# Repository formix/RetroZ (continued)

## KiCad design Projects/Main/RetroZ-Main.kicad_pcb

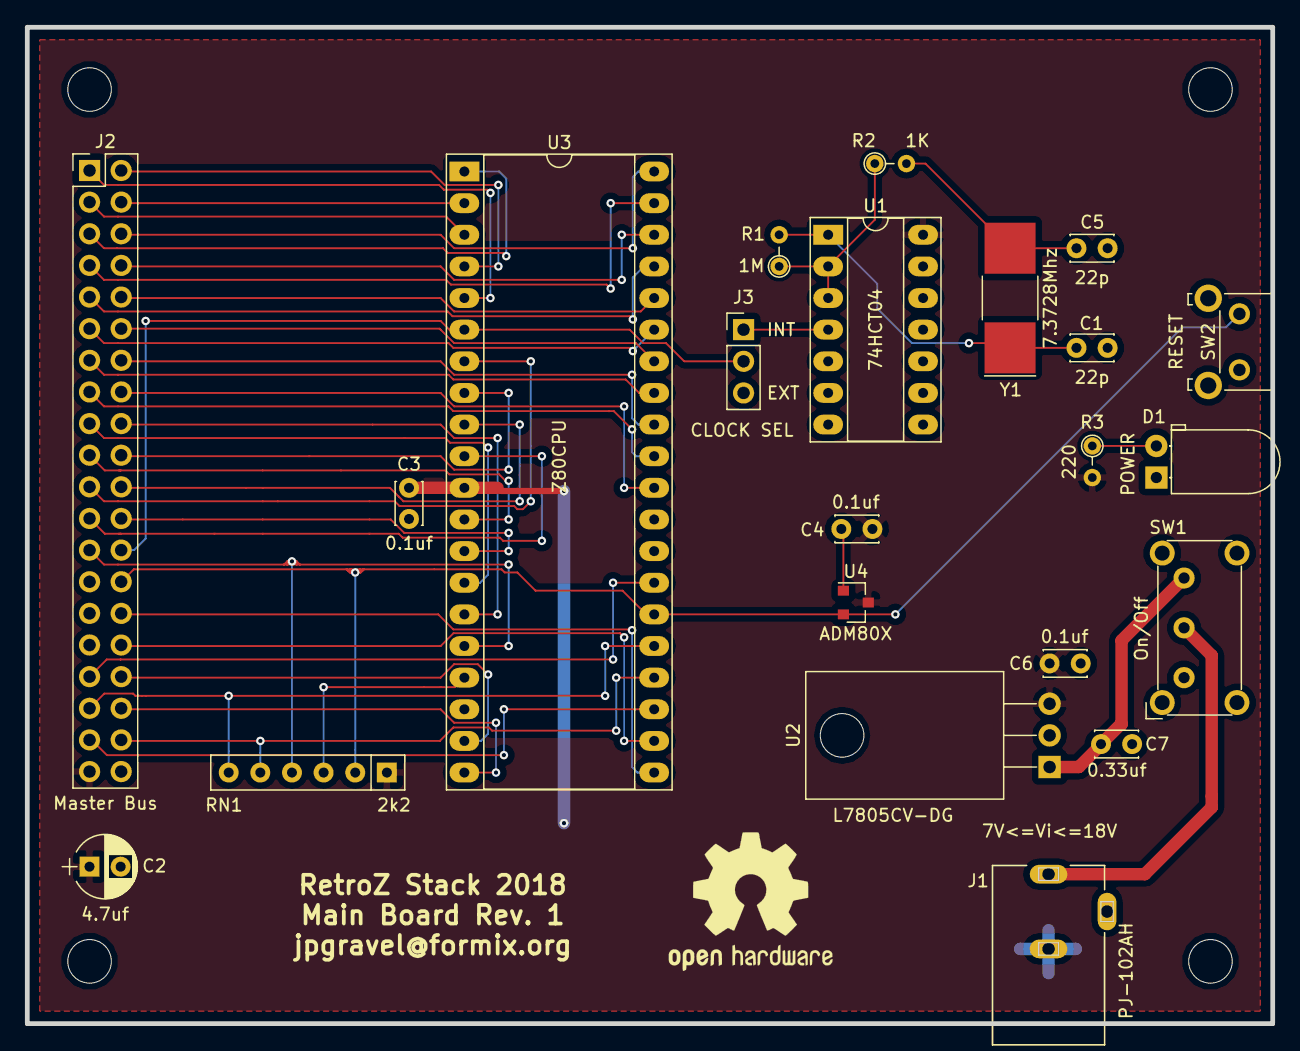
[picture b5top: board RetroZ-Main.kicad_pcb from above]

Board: 2 copper layers, 100.0 x 80.0 mm, 22 parts (0 on the bottom side), 45 nets.

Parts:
C1, C5: 22p; C_Disc_D3.4mm_W2.1mm_P2.50mm
C2: 4.7uf; CP_Radial_D5.0mm_P2.50mm
C3, C4, C6: 0.1uf; C_Disc_D3.4mm_W2.1mm_P2.50mm
C7: 0.33uf; C_Disc_D3.4mm_W2.1mm_P2.50mm
D1: POWER; LED_D5.0mm_Horizontal_O1.27mm_Z3.0mm
J1: PJ-102AH; CUI_PJ-102A
J2: Master Bus; Pin_Header_Straight_2x20_Pitch2.54mm
J3: CLOCK SEL; Pin_Header_Straight_1x03_Pitch2.54mm
R1: 1M; R_Axial_DIN0204_L3.6mm_D1.6mm_P2.54mm_Vertical
R2: 1K; R_Axial_DIN0204_L3.6mm_D1.6mm_P2.54mm_Vertical
R3: 220; R_Axial_DIN0204_L3.6mm_D1.6mm_P2.54mm_Vertical
RN1: 2k2; R_Array_SIP6
SW1: On/Off; SW_E-Switch_EG1224_SPDT_Angled
SW2: RESET; SW_Tactile_SKHH_Angled
U1: 74HCT04; DIP-14_W7.62mm_Socket_LongPads
U2: L7805CV-DG; TO-220-3_Horizontal
U3: Z80CPU; DIP-40_W15.24mm_Socket_LongPads
U4: ADM80X; SOT-23
Y1: 7.3728Mhz; Crystal_SMD_SeikoEpson_MC405-2pin_9.6x4.1mm

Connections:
/A0: J2.16, U3.30
/A1: J2.15, U3.31
/A2: J2.14, U3.32
/A3: J2.13, U3.33
/A4: J2.12, U3.34
/A5: J2.11, U3.35
/A6: J2.10, U3.36
/A7: J2.9, U3.37
/A8: J2.8, U3.38
/A9: J2.7, U3.39
/A10: J2.6, U3.40
/A11: J2.5, U3.1
/A12: J2.4, U3.2
/A13: J2.3, U3.3
/A14: J2.2, U3.4
/A15: J2.1, U3.5
/D0: J2.17, U3.14
/D1: J2.18, U3.15
/D2: J2.19, U3.12
/D3: J2.20, U3.8
/D4: J2.21, U3.7
/D5: J2.22, U3.9
/D6: J2.23, U3.10
/D7: J2.24, U3.13
CLK: J2.26, J3.2, U3.6
GND: C1.2, C2.2, C3.2, C4.2, C5.2, C6.2, C7.2, D1.1, J1.2, J2.40, SW2.2, U1.7, U2.2, U3.29, U4.1
unnamed: C1.1, R1.2, U1.1, Y1.1
unnamed: C5.1, R2.2, Y1.2
unnamed: C7.1, SW1.3, U2.1
unnamed: D1.2, R3.1
unnamed: J1.1, SW1.2
unnamed: J3.1, U1.4
unnamed: R1.1, R2.1, U1.2, U1.3
unnamed: RN1.3, U3.17
VCC: C2.1, C3.1, C4.1, C6.1, J2.39, R3.2, RN1.1, U1.14, U2.3, U3.11, U4.3
~BUSACK: J2.37, U3.23
~BUSRQ: J2.35, RN1.6, U3.25
~INT: J2.25, RN1.4, U3.16
~IORQ: J2.36, U3.20
~M1: J2.33, U3.27
~MREQ: J2.34, U3.19
~RD: J2.30, U3.21
~RESET: J2.28, RN1.2, SW2.1, U3.26, U4.2
~WAIT: J2.38, RN1.5, U3.24
~WR: J2.32, U3.22

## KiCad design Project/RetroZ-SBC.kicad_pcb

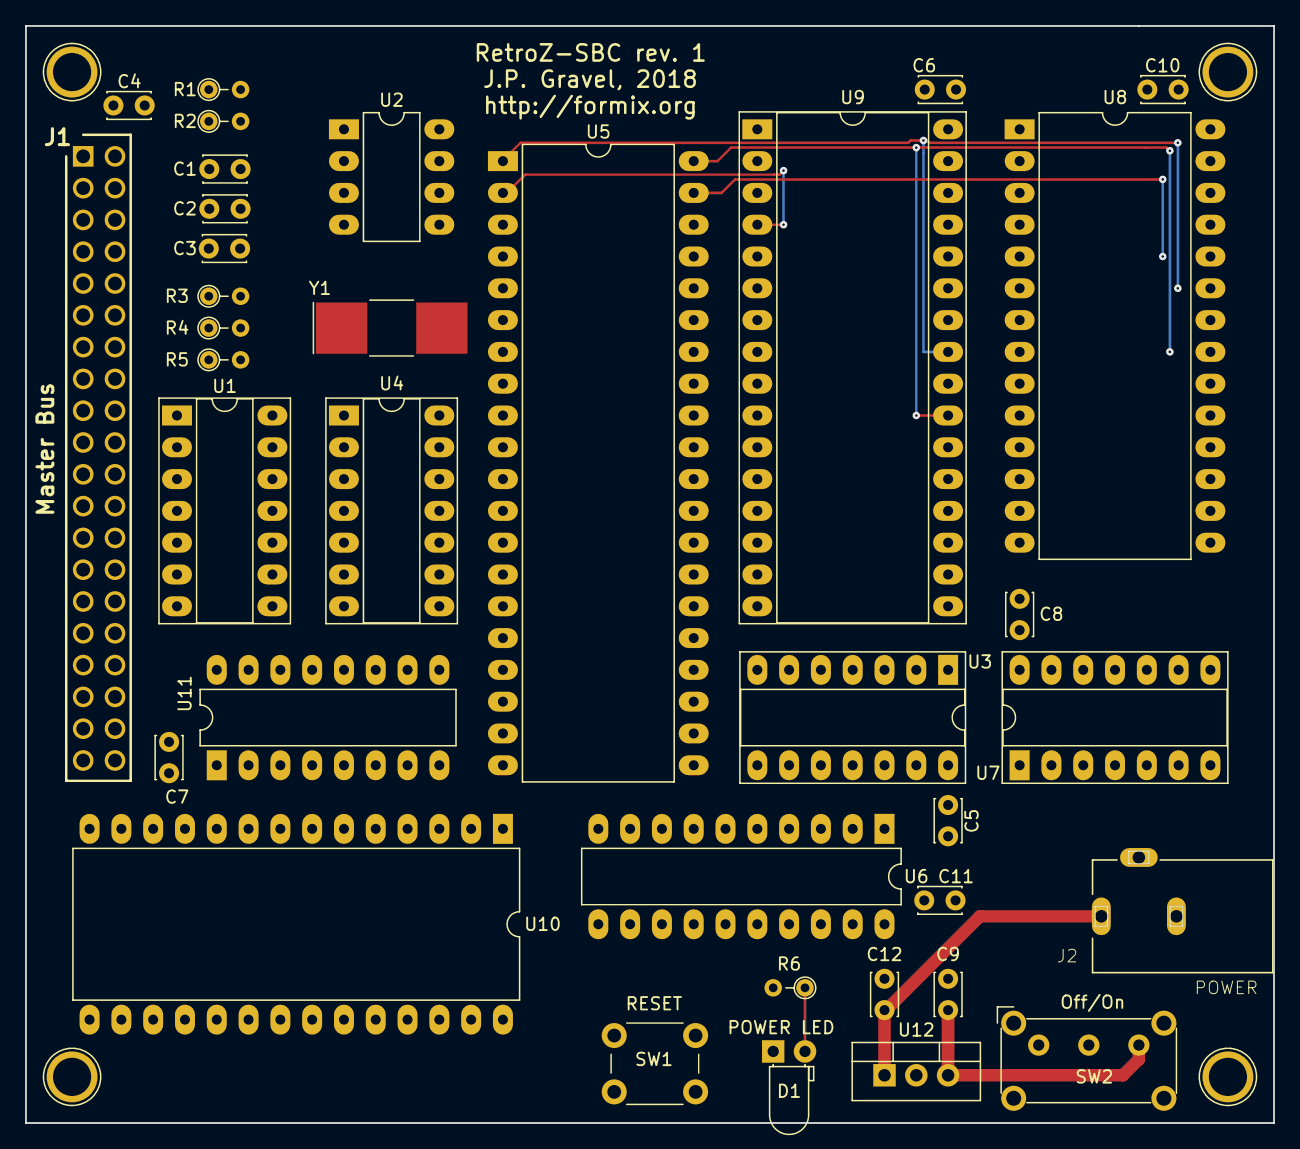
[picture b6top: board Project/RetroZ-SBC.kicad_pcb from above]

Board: 4 copper layers, 99.7 x 87.6 mm, 36 parts (0 on the bottom side), 74 nets.

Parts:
C1, C2: 22p; C_Disc_D3.4mm_W2.1mm_P2.50mm
C3, C4, C5, C6, C7, C8, C9, C10, C11: 0.1uf; C_Disc_D3.4mm_W2.1mm_P2.50mm
C12: 0.33uf; C_Disc_D3.4mm_W2.1mm_P2.50mm
D1: POWER LED; LED_D3.0mm_Horizontal_O1.27mm_Z2.0mm
J1: Master Bus; SHDR40W64P254_2X20_5130X500X865P
J2: POWER; CUI_PJ-102A
R1: 1M; R_Axial_DIN0204_L3.6mm_D1.6mm_P2.54mm_Vertical
R2: 1K; R_Axial_DIN0204_L3.6mm_D1.6mm_P2.54mm_Vertical
R3, R4, R5: 10k; R_Axial_DIN0204_L3.6mm_D1.6mm_P2.54mm_Vertical
R6: 100; R_Axial_DIN0204_L3.6mm_D1.6mm_P2.54mm_Vertical
SW1: RESET; SW_PUSH_6mm_h5mm
SW2: Off/On; SW_E-Switch_EG1224_SPDT_Angled
U1: 74HCT04; DIP-14_W7.62mm_Socket_LongPads
U2: max699cpa; DIP-8_W7.62mm_LongPads
U3: 74LS32; DIP-14_W7.62mm_Socket_LongPads
U4: 74LS08; DIP-14_W7.62mm_Socket_LongPads
U5: Z80CPU; DIP-40_W15.24mm_LongPads
U6: 74HC273; DIP-20_W7.62mm_LongPads
U7: 74LS08-And2; DIP-14_W7.62mm_Socket_LongPads
U8: AT28C64B-15PU; DIP-28_W15.24mm_LongPads
U9: AS6C4008-55PCN; DIP-32_W15.24mm_Socket_LongPads
U10: Z84C3008PEG; DIP-28_W15.24mm_LongPads
U11: 74LS138; DIP-16_W7.62mm_LongPads
U12: L7805CV-DG; TO-220-3_Vertical
Y1: 7.3728Mhz; Crystal_SMD_SeikoEpson_MC405-2pin_9.6x4.1mm

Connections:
/A4: U5.34, U8.6, U9.8, U11.1
/A5: U5.35, U8.5, U9.7, U11.2
/A6: U5.36, U8.4, U9.6, U11.3
/A8: U5.38, U8.25, U9.27
/A9: U5.39, U8.24, U9.26
/A10: U5.40, U8.21, U9.23
/A11: U5.1, U8.23, U9.25
/A12: U5.2, U8.2, U9.4
/A13: U3.9, U5.3, U9.28
/A14: U3.10, U5.4, U9.3
/D0: J1.26, U5.14, U6.3, U8.11, U9.13, U10.25
/D1: J1.27, U5.15, U6.4, U8.12, U9.14, U10.26
/D2: J1.28, U5.12, U6.7, U8.13, U9.15, U10.27
/D3: J1.29, U5.8, U6.8, U8.15, U9.17, U10.28
/D4: J1.30, U5.7, U6.13, U8.16, U9.18, U10.1
/D5: J1.31, U5.9, U8.17, U9.19, U10.2
/D6: J1.32, U5.10, U8.18, U9.20, U10.3
/D7: J1.33, U5.13, U8.19, U9.21, U10.4
A0: J1.34, U5.30, U8.10, U9.12, U10.18
A1: J1.35, U5.31, U8.9, U9.11, U10.19
A2: J1.36, U5.32, U8.8, U9.10
A3: J1.37, U5.33, U8.7, U9.9
A7: J1.38, U5.37, U8.3, U9.5, U11.5
A15: U3.13, U4.5, U5.5
CLK: J1.39, U1.4, U4.2, U5.6, U10.15
CLK0: J1.23, U10.7
CLK1: J1.24, U10.8
CLK2: J1.25, U10.9
GND: C1.2, C2.2, C3.2, C4.2, C5.2, C6.2, C7.2, C8.2, C9.2, C10.2, C11.2, C12.2, D1.1, J1.40, J2.2, SW1.1, U1.7, U2.3, U2.4, U2.8, U3.7, U4.7, U5.29, U6.10, U6.14, U6.17, U6.18, U7.7, U8.14, U9.16, U10.5, U11.8, U12.2
IEO: J1.10, U10.11
unnamed: C1.1, R1.2, U1.1, Y1.1
unnamed: C2.1, R2.2, Y1.2
unnamed: C9.1, SW2.3, U12.3
unnamed: C12.1, J2.1, U12.1
unnamed: D1.2, R6.1
unnamed: R1.1, R2.1, U1.2, U1.3
unnamed: U1.6, U4.1
unnamed: U1.8, U4.10
unnamed: U1.9, U3.11
unnamed: U1.10, U4.9
unnamed: U3.1, U3.5, U5.19
unnamed: U3.8, U3.12
unnamed: U4.3, U6.11
unnamed: U4.6, U7.2, U7.5, U7.10, U7.13
unnamed: U6.2, U7.1
unnamed: U6.5, U7.4
unnamed: U6.6, U7.9
unnamed: U6.9, U7.12
RAMONLY: U1.11, U4.4, U6.12
RAM_A15: U7.3, U9.31
RAM_A16: U7.6, U9.2
RAM_A17: U7.8, U9.30
RAM_A18: U7.11, U9.1
VCC: C3.1, C4.1, C5.1, C6.1, C7.1, C8.1, C10.1, C11.1, J1.1, R3.2, R4.2, R5.2, R6.2, SW2.2, U1.14, U2.1, U2.2, U3.14, U4.14, U5.11, U5.17, U5.25, U6.20, U7.14, U8.27, U8.28, U9.32, U10.13, U10.24, U11.6, U11.16
~HALT: J1.6, U5.18
~INT: J1.8, R3.1, U5.16, U10.12
~IO0: J1.11, U1.5, U11.15
~IO1: J1.12, U10.16, U11.14
~IO2: J1.13, U11.13
~IO3: J1.14, U11.12
~IO4: J1.15, U11.11
~IO5: J1.16, U11.10
~IO6: J1.17, U11.9
~IO7: J1.18, U11.7
~IORQ: J1.3, U5.20, U10.10, U11.4
~M1: J1.2, U5.27, U10.14
~MRD: U3.3, U8.22, U9.24
~MWR: U3.6, U9.29
~RAM_SEL: U1.13, U4.8, U9.22
~RD: J1.4, U3.2, U5.21, U10.6
~RESET: J1.9, R5.1, SW1.2, U2.7, U5.26, U6.1, U10.17
~ROM_SEL: U1.12, U8.20
~WAIT: J1.7, R4.1, U5.24
~WR: J1.5, U3.4, U5.22

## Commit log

2018-08-18 first commit... maybe?
2018-08-18 moved to another design with Serial Basic module
2018-08-20 dunno!
2018-08-20 deleted no reset btn comment
2018-08-21 initial layout
2018-08-21 started the physical layout
2018-08-22 started the layout
2018-08-22 added some data wires
2018-08-23 fixed the ratnest!
2018-08-25 current state
2018-08-30 new master bus design
2018-09-03 removed ctc
2018-09-03 deleted systembus
2018-09-03 removed all '-SBC' values
2018-09-03 splitted main and memory units
2018-09-03 remade the main board
2018-09-03 finished main board
2018-09-06 memory board halfway
2018-09-09 restructuration du dossier de projet
2018-09-11 sio2+ctc
2018-09-22 added usb to serial with an FT230XS-U chip
2018-09-22 in the process of updating the bus and fixing memory board mega-issue!
2018-09-22 fixed Processor Board
2018-09-22 added the issue list
2018-09-22 Renamed the issues file for 'todo'
2018-09-22 created README
2018-09-22 readme.md
2018-10-02 terminated the memory board
2018-10-02 fixed the bus and removed RxTx from the ctc-sio2 board
2018-10-05 finished sio2 board
2018-10-05 reflowed
2018-10-14 fixed a bunch of issues with the main board and some on the memory board
2018-10-16 changed power-on reser chip
2018-10-17 fixing memory access time
2018-10-17 added quad nor to accelerate memory chip select decoding
2018-10-17 simplified schematic
2018-10-17 adjusted configuration for JLCPCB plotting
2018-10-30 completed Main BOM
2018-10-31 added some rescue files
2018-11-11 added BOMs
2018-11-16 updated BOM and changed on capacitor
2018-12-31 SBC First commit!
2018-12-31 udated link reference
2018-12-31 added missing href
2018-12-31 typo
2019-01-03 added a dip switch to toggle the computer power
2019-01-03 fixed a typo
2019-01-03 updated the lib table
2019-01-06 updated readme.md and some schematic texts
2019-01-06 moved some high speed signals traces away from other traces
2019-01-06 added stacking header notice
2019-01-06 added precisions on the S80 project
2019-01-06 corrected some typos
2019-01-10 added the cache file
2019-01-10 increased the width of a VCC trace
2019-01-15 updated the git ignore
2019-01-15 added pull-up resistors and comments
2019-01-16 moved interrupts to user port A
2019-01-20 added missing pull-ups and changed git status
2019-01-20 updated a few lables
2019-01-20 added an url to the board
2019-01-20 removed stacking header notice
2019-01-20 updated readme again
2019-01-26 added BOM information
2019-01-26 added the bom to README
2019-01-26 fixed some doc issue
2019-01-26 added the desctiption to the BOM
2019-02-06 fixed the 1M/1k resistor inversion issue!
2019-02-09 added Sio/2 Basic 32k RAM
2019-02-09 removed my test code
2019-02-09 added basic asm folders
2019-02-13 sio test
2019-02-13 added missing asm
2019-02-17 adding tetris game
2019-02-17 adding asm sinus function
2019-02-18 sio tests
2019-02-19 moved some files around
2019-03-02 sinusoid 2
2019-03-03 sinusoid2 added functions
2019-03-03 added print space test
2019-03-03 sinusoid2 finished!
2019-03-08 made some changes...
2019-03-09 fixed reading issue
2019-03-09 sio-init fixedgit statusgit status
2019-03-10 Fixed initialization issuegit status!
2019-03-10 added a WAIT function
2019-03-10 udapted comment
2019-03-13 ITOA implementedgit statusgit status
2019-03-14 ITOA can now convert up to base 16
2019-03-31 added a bunch of VT102 functions!
2019-04-02 fixed multiple issues, added DRAW_RECT
2019-06-12 added the S80 Library
2019-07-23 started library v2
2019-07-24 moved sio2 code into the new library
2019-08-03 Updated README and testing new dev concept
2019-08-03 updated a readme sentence
2019-08-09 added the template
2019-08-09 deleted some files
2019-08-12 Fixed the template issue
2019-08-12 renamed the template file
2019-08-12 created the RetroZ-RAM24K extension
2019-08-13 adding footprints...
2019-08-29 implemented SCREEN statement!
2019-08-29 added comments
2019-08-30 started fixing the screen code
2019-09-08 successfully added the screen command
2019-09-08 modified the comment
2019-09-08 made better comment
2019-09-08 clarified comments further
2019-09-09 added the roulette program
2019-09-10 added the color statement
2019-10-14 removed SD disk io from SMBaker
2019-10-14 multiple z80 experiments
2019-10-14 Trying out the new screen instruction
2019-10-14 changed screen param interpretation to 8 bits
2019-10-14 changed the fg color interpretation to 8 bits
2019-10-14 changed BG parsing to 8 bits
2019-10-14 color 100% implemented
2019-10-15 finished the demo gunman2.bas
2020-01-13 added the RetroZ-disk
2020-01-30 Created the schematic
2020-03-06 RetroZ disk design done
2020-03-12 added interrupt signal
2020-03-12 fixed interrupt ack processing
2020-03-27 removed interrupt management, added arduino code
2020-03-29 commit a hugge change set
2020-03-29 fixed typo
2020-03-30 started testing comm with RetroZ
